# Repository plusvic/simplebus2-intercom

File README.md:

Overview
--------

Simplebus2 is a two-wire door entry system created by the Italian company Comelit. It supports both audio and video, and it's widely used in residential buildings, specially across Europe.

The building where I live has one of those systems, so I wanted to understand how it worked in order to solve a practical problem: getting notified when someone is ringing my doorbell. I work from home and usually wear noise-cancelling headphones while working, which means that I can't hear the doorbell. I wanted to install a complementary notification system, such as a light that turns on, or something that vibrates on my desk.

In this project I'm sharing my findings about how the Simplebus2 system works, and a detailed description of the devices I've built.

How it works
------------

The Simplebus2 door entry system uses only two wires for carrying both DC power and signals to the intercom devices installed on each apartment. All the devices share the same two wires, hence the "bus" word in the name. Those two wires are not polarized, they are labeled the same way (L) and can be connected arbitrarily to the intercom devices. Of course, being DC there's a GND and a Vcc, but devices are prepared to accept both wires in any of the two possible ways. This is done by putting a full-bridge rectifier at the device's input.

The DC voltage in the bus is 22-34V according to the manufacturer (in my particular case it is 26.5V), and signals are mounted on top of this DC offset. When someone calls an apartment from the building's entry door, a message is transmitted over the bus. All the intercom units in the building can see the message, but only the unit in the target apartment reacts to the message. Each intercom unit has its own 8-bits address, which is configured via a 8-way DIP switch during installation. See the interior of a Comelit 2738W intercom with the DIP switch in red:

Multiple units can share the same address, this is common practice when two or more intercoms are installed in the same apartment. Simplebus2 messages are 18-bits long, structured as follows:

* 6 bits for the message code

* 8 bits for the intercom address

* 4 bits for the checksum

Messages are transmitted using pulse length encoding, where each bit consists in a burst of pulses at 25kHz during 3ms, followed by a silence that can be 3ms or 6ms long. The length of the silence determines the bit's value, 3ms for zero, 6ms for one. Messages start with a preamble consisting in the 3ms burst followed by a 17ms silence. The first bit is transmitted right after the preamble.

The image above shows the capture of a message with an oscilloscope, the yellow stripes are the 25kHz bursts, which have always the same width because they are all 3ms long. You can also see that the space in between the bursts are not homogeneous, some spaces are wider than others, the wider ones (6ms) represent the 1s, the narrower (3ms) are 0s. The preamble can be also clearly appreciated. 

The bits in green correspond to the message code, the ones in red are the intercom's address, and the checksum is shown in yellow. The least significant bit (LSB) is sent first, so the actual values are:

Message code:  110000 = 48

Address: 00001100 = 12

Checksum: 0100 = 4

The checksum is simply the number of bits that are set to 1 in the message code and address. In this case the checksum is 4 because there are four bits set, two in the message code and two in the address. Notice how the address matches the position of the DIP switches in the first picture, and curiously enough the most significant bits in the switch are at the right, so the order of the bits is identical in the switch and in the oscilloscope capture. I live at the 6th floor of a building with two apartments per floor, so it make sense that my intercom has address 12, if the installer was being meticulous my next door neighbor should have address 11, and the apartment just below mine should have address 10.

Right after the message (at the right end of the oscilloscope capture) you can see four bursts separated by 3ms silences, those are not part of the message itself, that's a response from the target intercom acknowledging that the message has been received. The amplitude of the acknowledgement signal is clearly higher because the source of that signal is the intercom in my house, which is close to the point where the oscilloscope was connected, while the message comes from the building's entry door, which is further away and therefore arrives attenuated.

These are some of the supported message codes, but bear in mind that some descriptions may be inaccurate as I've have deduced their meaning based on experimentation.

| Code     | Description                                                                                      |
|----------|--------------------------------------------------------------------------------------------------|
| 16 | Open door. Sent from intercoms to the building's entry door when you pulse the open door button.       |
| 17 | Handset hook off |
| 18 | Handset hook on. |
| 19 |	Call switchboard.	|
| 20 |	Turn on door camera and video screen.	|
| 21 | Floor door's ring tone. Intercoms have a pair of terminals labeled CFP (which are visible in the picture above), these terminals are for connecting a push button at your apartment's door. This message is sent by the intercom when it detects that its CFP terminals are connected together, so that all the other intercom's installed in the apartment start ringing. |
| 48 | Building door's ring tone. Send from the building's entry door when someone is calling your apartment. For each of these messages the intercom rings once, the full calling sequence is two messages with code 48 followed by a message with code 50. |
| 50 | Building door's ring tone and end of call. When this message is received the intercom ring in the same way it does with message 48, but also turns on the video screen. |

The devices
-----------

Once I understood how the Simplebus2 protocol worked, it was time for building a device that could notify me when someone ring my doorbell. The requisites were:

* The device should be powered from the bus in the same way the real intercom does. 

* It should fit in some empty space inside a Comelit 2738W casing.  

* Any notification sent by the device should be transmitted wireless to some other receiving device close to my desk.

The first two requisites were easy to fulfill, the bus provides enough power for the Comelit 6701W video intercom,  which consumes 5.4W according to its datasheet, our device should a require just a fraction of that. Also, the Comelit 2738W, has 30x60x15mm empty cavity that looked big enough for holding my device.

The third requisite was the one that needed more experimentation. I created a first prototype based in a [433MHz transmitter/receiver kit](https://randomnerdtutorials.com/rf-433mhz-transmitter-receiver-module-with-arduino/) with the transmitter inside the intercom sending the signals seen in the bus to the receiver in my desk, connected to an Arduino board. But this was unidirectional, I could receive messages from the intercom, but couldn't send messages back, for example for opening the door directly from my desk. I wanted a bi-directional communication channel, so I tried an [ESP8266](https://en.wikipedia.org/wiki/ESP8266) connected to my WiFi network, but the ESP8266 was very power-hungry. Finally a resorted to a pair of [HC-12](https://howtomechatronics.com/tutorials/arduino/arduino-and-hc-12-long-range-wireless-communication-module/) wireless serial communication modules that worked like a charm. 

The final setup was:

* A simple circuit with a PIC12F508 decodes the Simplebus2 messages and send them via UART to an HC-12 module. The HC-12 module transmit the message wirelessly. All of this stuff was put into the empty cavity of my Comelit 2738W intercom.

* At the other end (in my desk) another HC-12 module receives the wireless message and passes it to a [Wemos D1 mini](https://www.wemos.cc/en/latest/d1/d1_mini.html) board.

* The Wemos D1 mini controls a led strip that flashes when someone is calling my door and a haptic motor that produces some vibration. 

* Messages can also travel the other way around from the Wemos D1 mini to the PIC12F508 via the two HC-12 modules, and the PIC12F508 produces the signals that are transmitted over the bus.

The circuit that decodes the Simplebus2 messages is shown below:

The bridge rectifier (DB1) fixes the polarity of the input, so that the Simplebus2 wires can be connected in any way without having to take their polarity into account. A low-pass filter (R1 and C1) removes the voltage fluctuations produced by signals and feeds the base DC to the LM7805 voltage regulator that provides 5V to the other components. A high-pass filter (R2 and C3) removes the DC component on the Simplebus2 line allowing the signals pass to the non-inverting input of a LM2903 comparator. The comparator's inverting input receives a reference voltage of around 500mV produced by the voltage divider (R3 and R4).

The comparator's output is fed into the PIC12F508 microcontroller, which decodes the messages and re-transmitted via UART to the HC-12 transceiver module. The Q1 transistor is used for transmitting messages through the bus, it is usually in cutoff mode, but the microcontroller allows current to pass through the transistor for brief intervals causing the voltage changes in the bus that will conform the message. The program that runs inside the PIC12F508 can be found [here](repeater/simplebus2-repeater.asm).

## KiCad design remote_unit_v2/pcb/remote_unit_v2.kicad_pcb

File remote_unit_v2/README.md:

# Project template for rp2040-hal

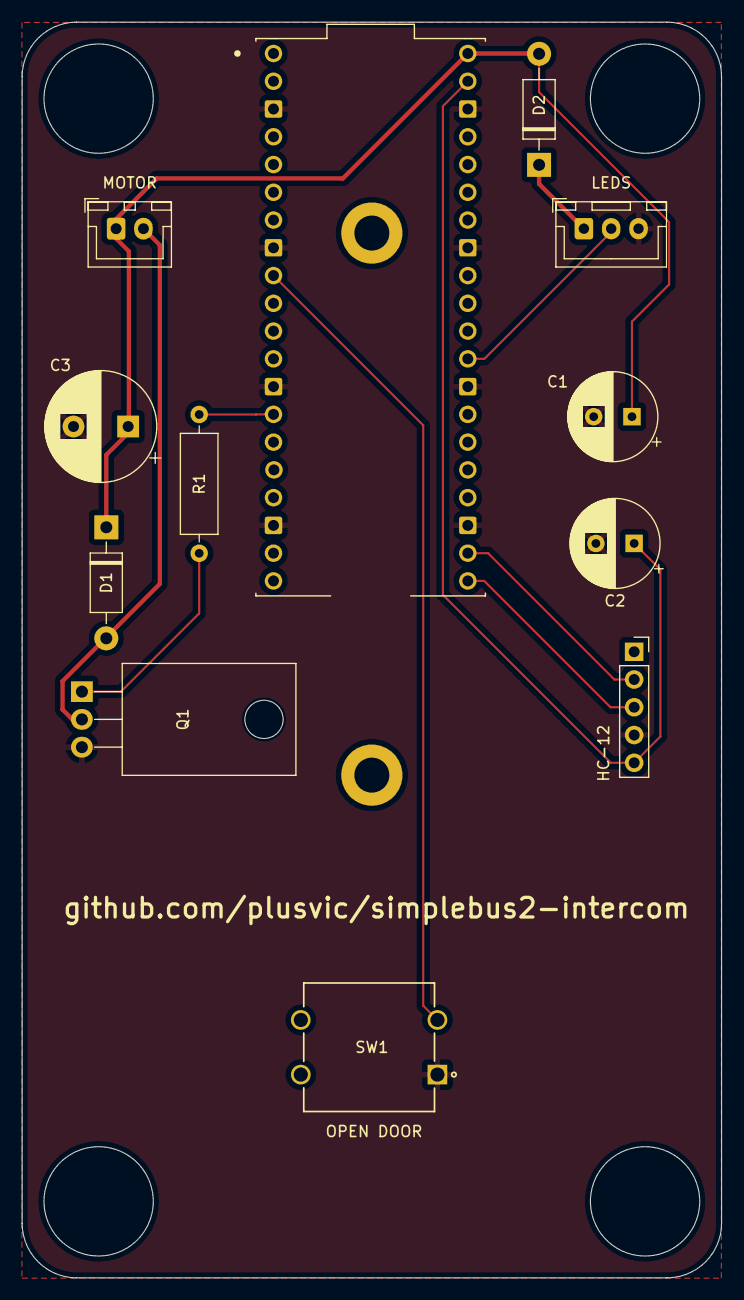
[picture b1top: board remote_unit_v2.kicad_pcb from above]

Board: 2 copper layers, 64.0 x 114.9 mm, 12 parts (0 on the bottom side), 11 nets.

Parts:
A1: SC0918; MODULE_SC0918
C1, C2: 470uF; CP_Radial_D8.0mm_P3.50mm
C3: 680uF; CP_Radial_D10.0mm_P5.00mm
D1, D2: 1N4001; D_DO-41_SOD81_P10.16mm_Horizontal
J1: LEDS; JST_XH_B3B-XH-A_1x03_P2.50mm_Vertical
J2: HC-12; PinSocket_1x05_P2.54mm_Vertical
J3: MOTOR; JST_XH_B2B-XH-A_1x02_P2.50mm_Vertical
Q1: Q_NPN_Darlington_BCE; TO-220-3_Horizontal_TabDown
R1: 1k; R_Axial_DIN0309_L9.0mm_D3.2mm_P12.70mm_Horizontal
SW1: OPEN DOOR; COM-10302_SPK

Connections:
3.3V: A1.39 (VSYS), C2.1, J2.5
/RX: A1.21 (GP16), J2.3
/TX: A1.22 (GP17), J2.2
GND: A1.3 (GND), A1.8 (GND), A1.13 (GND), A1.18 (GND), A1.23 (GND), A1.28 (GND), A1.33 (AGND), A1.38 (GND), C1.2, C2.2, C3.2, J1.3, J2.4, Q1.3 (E), SW1.1
unnamed: A1.9 (GP6), SW1.3 (K)
unnamed: A1.14 (GP10), R1.2
unnamed: A1.29 (GP22), J1.2
unnamed: D1.2 (A), J3.2, Q1.2 (C)
unnamed: D2.1 (K), J1.1
unnamed: Q1.1 (B), R1.1
VBUS: A1.40 (VBUS), C1.1, C3.1, D1.1 (K), D2.2 (A), J3.1

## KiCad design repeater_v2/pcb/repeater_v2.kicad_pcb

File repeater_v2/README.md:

# repeater

## Prerequisites

  * A recent version of the nightly Rust compiler. Anything including or
    greater than `rustc 1.63.0-nightly (fee3a459d 2022-06-05)` can be used.
  * The rust-src rustup component - `$ rustup component add rust-src`
  * AVR-GCC on the system for linking
  * AVR-Libc on the system for support libraries
  * minipro (https://gitlab.com/DavidGriffith/minipro)

## How to build

This project must be built with a nightly version of rustc because we must use the 
`-Z build-std=core` in order to build the `core` standard library.

```bash
cargo build -Z build-std=core --target attiny85.json --release
objcopy -O ihex target/attiny85/release/repeater_v2.elf target/attiny85/release/repeater_v2.hex
minipro -w target/attiny85/release/repeater_v2.hex -p ATTINY85@DIP8
```

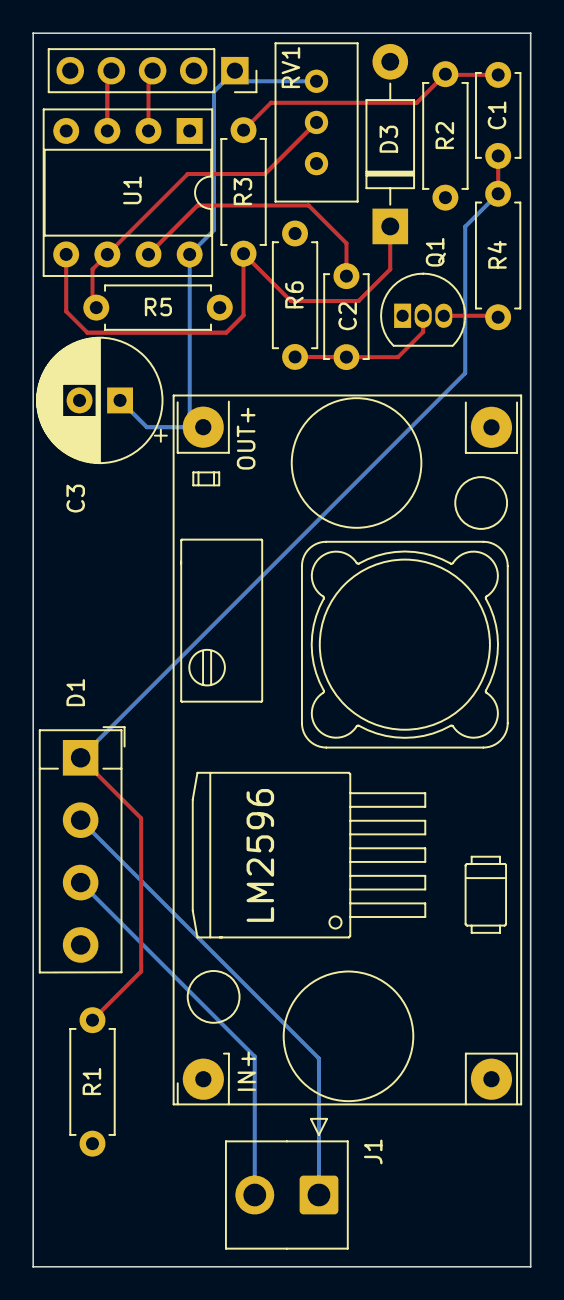
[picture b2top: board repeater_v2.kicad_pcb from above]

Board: 2 copper layers, 30.7 x 76.1 mm, 17 parts (0 on the bottom side), 13 nets.

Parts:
C1: 0.1uF; C_Disc_D5.0mm_W2.5mm_P5.00mm
C2: 100nF; C_Disc_D5.0mm_W2.5mm_P5.00mm
C3: 1000uF; CP_Radial_D7.5mm_P2.50mm
D1: Bridge Rectifier; Diode_Bridge_Vishay_KBPM
D3: 1N47xxA; D_DO-41_SOD81_P10.16mm_Horizontal
IN+: YAAJ_DCDC_StepDown_LM2596
J1: SimpleBus Connector; TE_826576-2_1x02_P3.96mm_Vertical
J2: HC-12; PinSocket_1x05_P2.54mm_Vertical
Q1: PN2222A; TO-92_Inline
R1: 560R; R_Axial_DIN0207_L6.3mm_D2.5mm_P7.62mm_Horizontal
R2, R5: 10k; R_Axial_DIN0207_L6.3mm_D2.5mm_P7.62mm_Horizontal
R3: 100; R_Axial_DIN0207_L6.3mm_D2.5mm_P7.62mm_Horizontal
R4: 220R; R_Axial_DIN0207_L6.3mm_D2.5mm_P7.62mm_Horizontal
R6: 2.2k; R_Axial_DIN0207_L6.3mm_D2.5mm_P7.62mm_Horizontal
RV1: 3298; Potentiometer_Bourns_3296W_Vertical
U1: ATtiny85-20P; DIP-8_W7.62mm_Socket

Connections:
+5V: C3.1, IN+.4, J2.1, RV1.1, U1.8 (VCC)
GND: C3.2, D1.4 (-), D3.2 (A), IN+.2, IN+.3, J2.2, Q1.1 (E), R2.2, R5.2, R6.2, U1.4 (GND)
unnamed: C1.2, R2.1, R3.2
unnamed: C1.1, D1.1 (+), R1.1, R4.1
unnamed: D3.1 (K), R3.1, U1.5 (AREF/PB0)
unnamed: D1.2, J1.1
unnamed: D1.3, J1.2
unnamed: C2.2, Q1.2 (B), R6.1
unnamed: Q1.3 (C), R4.2
unnamed: C2.1, U1.7 (PB2)
REF VOLTAGE: R5.1, RV1.2, U1.6 (PB1)
UART RX: J2.4, U1.3 (XTAL2/PB4)
UART TX: J2.3, U1.2 (XTAL1/PB3)

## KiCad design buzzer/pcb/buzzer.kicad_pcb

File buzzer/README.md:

# buzzer

## Prerequisites

  * A recent version of the nightly Rust compiler. Anything including or
    greater than `rustc 1.63.0-nightly (fee3a459d 2022-06-05)` can be used.
  * The rust-src rustup component - `$ rustup component add rust-src`
  * AVR-GCC on the system for linking
  * AVR-Libc on the system for support libraries
  * minipro (https://gitlab.com/DavidGriffith/minipro)

## How to build

```bash
cargo build --release
objcopy -O ihex target/attiny13/release/buzzer.elf target/attiny13/release/buzzer.hex
minipro -w target/attiny13/release/buzzer.hex -p ATTINY13@DIP8
```

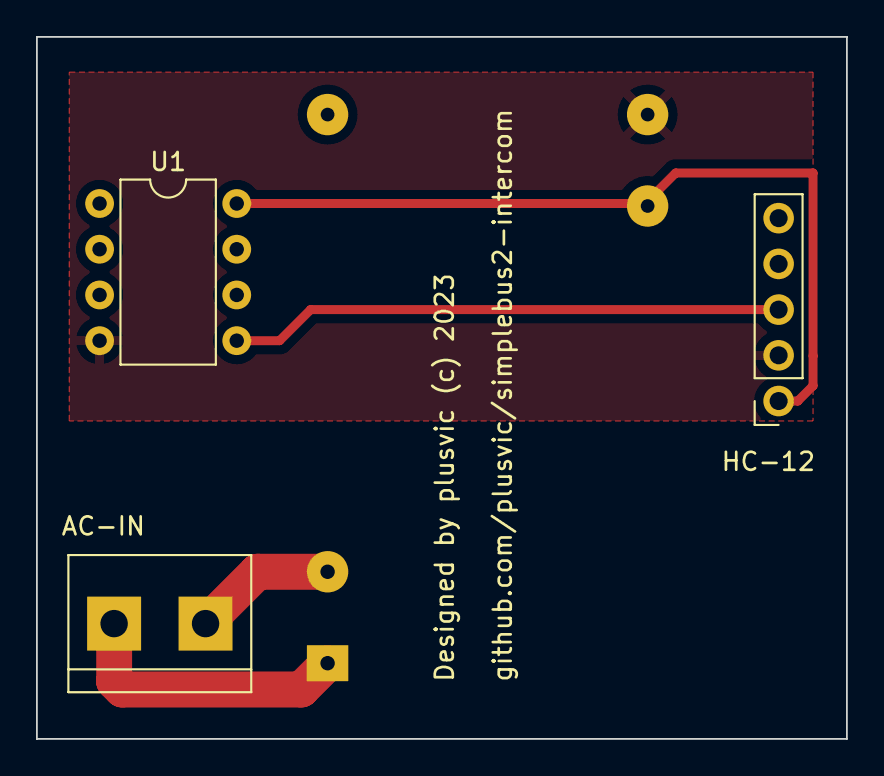
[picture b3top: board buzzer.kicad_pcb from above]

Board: 2 copper layers, 45.0 x 39.0 mm, 4 parts (1 on the bottom side), 5 nets.

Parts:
AC-IN: Screw_Terminal_01x02; TerminalBlock_bornier-2_P5.08mm
HC-12: Conn_01x05_Female; PinSocket_1x05_P2.54mm_Vertical
PS1: IRM-03-3.3; Custom_Converter_ACDC_MeanWell_IRM-03-xx_THT
U1: ATtiny13-20P; DIP-8_W7.62mm

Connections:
GND: HC-12.2, PS1.14 (-Vo), U1.4 (GND)
unnamed: HC-12.3, U1.5 (PB0)
unnamed: AC-IN.1, PS1.1 (AC/L)
unnamed: AC-IN.2, PS1.3 (AC/N)
Vcc: HC-12.1, PS1.16 (+Vo), U1.8 (VCC)

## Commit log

2021-05-23 Commit code for remote unit.
2021-05-23 Commit repeater's schematic and code.
2021-05-23 Update README.md
    Add details about the project.
2021-05-23 Fix bug in repeater's diagram.
2021-05-23 Add missing word to README.md
2021-10-29 Fix error un README.md
2021-11-05 Update remote unit code with latest changes.
2021-11-27 Implement silent mode and use InputDebounce library.
2023-01-22 Upgrade to Blynk 1.1.0
2023-07-30 Add buzzer.
    A simple Rust program for the ATtiny13 MCU that sends message 21 (MSG_CALL_FROM_FLOOR_DOOR) to the repeater using a HC-12 transceiver. Also contains the Kicad files for the hardware.
2024-12-27 Minor changes to buzzer.
2024-12-27 Add repeater v2
2024-12-27 Add remote unit v2
2024-12-27 Add repeater PCB files.
2024-12-27 Remove .idea directory
2024-12-30 Minor changes to remote unit v2
2025-01-25 Fix bug while decoding messages.
2025-01-25 Fix bugs.
2025-01-31 Improvements to remote unit v2

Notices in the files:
buzzer/pcb/buzzer.kicad_pcb:
Designed by plusvic (c) 2023
